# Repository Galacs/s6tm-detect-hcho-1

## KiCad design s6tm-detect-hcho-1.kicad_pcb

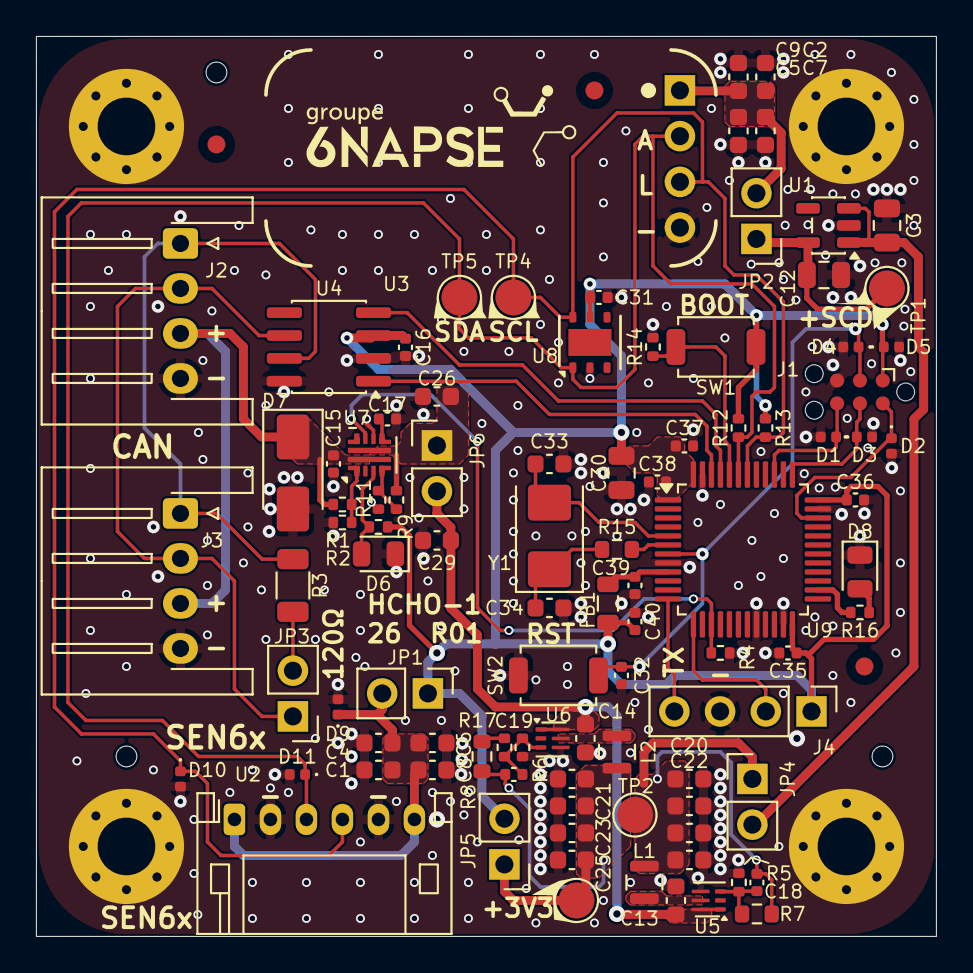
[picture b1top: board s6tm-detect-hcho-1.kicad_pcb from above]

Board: 2 copper layers, 50.0 x 50.0 mm, 106 parts (0 on the bottom side), 36 nets.

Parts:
C1, C2, C4, C5, C6, C7, C8, C9, C13, C14, C20, C21, C22, C23, C24, C25, C26, C27, C28, C29: 10u; C_0603_1608Metric
C3, C12, C30: 10u; C_0805_2012Metric
C15, C39, C40: 1u; C_0402_1005Metric
C16, C31, C32, C35, C36, C37, C38: 0u1; C_0402_1005Metric
C17: 1n; C_0402_1005Metric
C18, C19: 100p; C_0402_1005Metric
C33, C34: 20p; C_0603_1608Metric
D1, D2, D3, D4, D5, D9, D10, D11: H5VU10U; Diode_DFN1006
D6: GREEN; LED_0805_2012Metric
D7: SMAJ6.0CA; D_SMA
D8: YELLOW; LED_0805_2012Metric
FB1: 600Ω@100M; L_0805_2012Metric
FID1, FID2, FID3: Fiducial; Fiducial_1mm_Mask2mm
H1, H2, H3: MountingHole; ToolingHole_1.152mm
H4, H5, H6, H7: MountingHole_Pad; MountingHole_3.2mm_M3_Pad_Via
J1: TC2030; Tag-Connect_TC2030-IDC-NL_2x03_P1.27mm_Vertical
J2, J3: Conn_01x04; JST_XH_S4B-XH-A-1_1x04_P2.50mm_Horizontal
J4: Conn_01x04_Pin; PinHeader_1x04_P2.54mm_Vertical
JP1, JP2, JP3, JP4, JP5, JP6: Jumper_2_Small_Bridged; PinHeader_1x02_P2.54mm_Vertical
L1, L2: 0u47; TDK_TFM201610ALC
R1, R10, R12, R13, R14: 10k; R_0402_1005Metric
R2, R11: 4k7; R_0402_1005Metric
R3: 120; R_1206_3216Metric
R4: 3k3; R_0402_1005Metric
R5, R6: 100k; R_0402_1005Metric
R7: 510k; R_0603_1608Metric
R8: 430k; R_0603_1608Metric
R9, R16: 5k1; R_0402_1005Metric
R15: 560; R_0603_1608Metric
R17: 20k; R_0402_1005Metric
SW1, SW2: SW_Push; SW_SPST_TS-1088-xR020
TP1, TP2, TP3, TP4, TP5: TestPoint; TestPoint_Pad_D2.0mm
U1: TPS7A2033P; SOT-23-5
U2: SEN6x; JST_PH_S6B-PH-K_1x06_P2.00mm_Horizontal
U3: SCD43; Module_s6tm-scd4x-mod-1
U4: SN65HVD230; SOIC-8_3.9x4.9mm_P1.27mm
U5, U6: TPS6282x; Texas_VSON-6_1.5x1.5mm_P0.5mm_DMQ0006A
U7: TPS259472A; Texas_RPW0010A_VQFN-HR-10_2x2mm_P0.5mm
U8: HTU21; Texas_PWSON-N6
U9: STM32F103C8Tx; LQFP-48_7x7mm_P0.5mm
Y1: 8M; Crystal_SMD_5032-2Pin_5.0x3.2mm

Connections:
+3V3: C1.1, C4.1, C6.1, C8.1, C16.1, C19.1, C21.1, C23.1, C25.1, C28.1, C30.1, C31.2, C35.1, C36.1, C37.1, C38.1, C40.1, D5.1 (K), D9.1 (K), FB1.2, J1.1 (VCC), J4.1, JP1.1 (A), JP1.2 (B), JP5.1 (A), JP5.2 (B), L2.2, R8.1, R9.1, R12.1, R13.1, SW1.1, TP3.1 (1_1), U2.1 (VDD), U2.6 (VDD), U4.3 (VCC), U8.5 (VCC), U9.1 (VBAT), U9.24 (VDD), U9.36 (VDD), U9.48 (VDD)
+3V3_SCD: C2.1, C5.1, C7.1, C9.1, C12.1, JP2.1 (A), JP2.2 (B), TP1.1 (1_1), U1.5 (OUT), U3.7 (VDD)
+3V7: C3.1, C18.1, C20.1, C22.1, C24.1, C27.1, JP4.1 (A), JP4.2 (B), L1.2, R7.1, TP2.1 (1_1), U1.1 (IN), U1.3 (EN)
+5V: C13.1, C14.1, C26.1, C29.1, JP6.1 (A), JP6.2 (B), R10.2, U5.1 (EN), U5.6 (VIN), U6.1 (EN), U6.6 (VIN), U7.6 (OUT)
+5V_IN: C15.2, D7.1 (A1), J2.3, J3.3, R1.2, U7.5 (IN)
/BOOT: R14.2, SW1.2, U9.44 (BOOT0)
/CANH: J2.1, J3.1, R3.1, U4.7 (CANH)
/CANL: J2.2, J3.2, JP3.1 (A), U4.6 (CANL)
/CAN_RX: U4.4 (R), U9.45 (CAN_RX)
/CAN_TX: U4.1 (D), U9.46 (CAN_TX)
/ILM: R4.1, U7.9 (ILM), U9.15 (ADC1_IN5)
/NRST: C32.1, D4.1 (K), J1.3 (~RESET), SW2.2, U9.7 (NRST)
/SCL: D10.1 (K), R13.2, TP4.1 (1_1), U2.4 (SCL), U3.9 (SCL), U8.6 (SCL), U9.42 (I2C1_SCL)
/SDA: D11.1 (K), R12.2, TP5.1 (1_1), U2.3 (SDA), U3.10 (SDA), U8.1 (SDA), U9.43 (I2C1_SDA)
/SWCLK: D3.1 (K), J1.4 (SWCLK), U9.37 (SWCLK)
/SWDIO: D2.1 (K), J1.2 (SWDIO), U9.34 (SWDIO)
/SWO: D1.1 (K), J1.6 (SWO), U9.39 (TRACESWO)
/U0RXD: J4.2, U9.13 (USART2_RX)
/U0TXD: J4.4, U9.12 (USART2_TX)
/XTAL_I: C33.1, U9.5 (RCC_OSC_IN), Y1.2
/XTAL_O: R15.2, U9.6 (RCC_OSC_OUT)
/XTAL_RO: C34.1, R15.1, Y1.1
GND: C1.2, C2.2, C3.2, C4.2, C5.2, C6.2, C7.2, C8.2, C9.2, C12.2, C13.2, C14.2, C15.1, C16.2, C17.2, C20.2, C21.2, C22.2, C23.2, C24.2, C25.2, C26.2, C27.2, C28.2, C29.2, C30.2, C31.1, C32.2, C33.2, C34.2, C35.2, C36.2, C37.2, C38.2, C39.2, C40.2, D1.2 (A), D2.2 (A), D3.2 (A), D4.2 (A), D5.2 (A), D6.1 (K), D7.2 (A2), D8.1 (K), D9.2 (A), D10.2 (A), D11.2 (A), H4.1 (1_1), H5.1 (1_1), H6.1 (1_1), H7.1 (1_1), J1.5 (GND), J2.4, J3.4, J4.3, R2.1, R4.2, R5.2, R6.2, R11.1, R14.1, SW2.1, U1.2 (GND), U2.2 (GND), U2.5 (GND), U3.6 (GND), U4.2 (GND), U4.8 (Rs), U5.4 (GND), U6.4 (GND), U7.8 (GND), U8.2 (GND), U9.8 (VSSA), U9.20 (PB2), U9.23 (VSS), U9.35 (VSS), U9.47 (VSS)
unnamed: D6.2 (A), R9.2, U7.3 (PG)
unnamed: D8.2 (A), R16.2
unnamed: JP3.2 (B), R3.2
unnamed: R8.2, R17.2
unnamed: C18.2, R5.1, R7.2, U5.3 (FB)
unnamed: L1.1, U5.5 (SW)
unnamed: C19.2, R6.1, R17.1, U6.3 (FB)
unnamed: L2.1, U6.5 (SW)
unnamed: C17.1, U7.7 (DVDT)
unnamed: R1.1, R2.2, U7.1 (EN/UVLO)
unnamed: R10.1, R11.2, U7.4 (PGTH)
unnamed: R16.1, U9.26 (PB13)
unnamed: C39.1, FB1.1, U9.9 (VDDA)

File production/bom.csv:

Designator,Footprint,Quantity,Value,LCSC Part #
"C1, C13, C14, C2, C20, C21, C22, C23, C24, C25, C26, C27, C28, C29, C4, C5, C6, C7, C8, C9",0603,20,10u,C19702
"C12, C3, C30",0805,3,10u,C440198
"C15, C39, C40",0402,3,1u,C52923
"C16, C31, C32, C35, C36, C37, C38",0402,7,0u1,C307331
C17,0402,1,1n,C1523
"C18, C19",0402,2,100p,C1546
"C33, C34",0603,2,20p,C1648
"D1, D10, D11, D2, D3, D4, D5, D9",Diode_DFN1006,8,H5VU10U,C22395519
D6,0805,1,GREEN,C2297
D7,D_SMA,1,SMAJ6.0CA,C19077526
D8,0805,1,YELLOW,C2296
FB1,0805,1,600Ω@100M,C81034
"J2, J3",JST_XH_S4B-XH-A-1_1x04_P2.50mm_Horizontal,2,Conn_01x04,C163037
"L1, L2",TDK_TFM201610ALC,2,0u47,C89446
"R1, R10, R12, R13, R14",0402,5,10k,C25744
"R11, R2",0402,2,4k7,C25900
R15,0603,1,560,C23204
"R16, R9",0402,2,5k1,C25905
R17,0402,1,20k,C25765
R3,1206,1,120,C17909
R4,0402,1,3k3,C25890
"R5, R6",0402,2,100k,C25741
R7,0603,1,510k,C23192
R8,0603,1,430k,C25969
"SW1, SW2",SW_SPST_TS-1088-xR020,2,SW_Push,C720477
U1,SOT-23-5,1,TPS7A2033P,C2862740
U2,JST_PH_S6B-PH-K_1x06_P2.00mm_Horizontal,1,SEN6x,C157920
U4,SOIC-8_3.9x4.9mm_P1.27mm,1,SN65HVD230,C12084
"U5, U6",Texas_VSON-6_1.5x1.5mm_P0.5mm_DMQ0006A,2,TPS6282x,C2650334
U7,Texas_RPW0010A_VQFN-HR-10_2x2mm_P0.5mm,1,TPS259472A,C3662789
U8,Texas_PWSON-N6,1,HTU21,C83479
U9,LQFP-48_7x7mm_P0.5mm,1,STM32F103C8Tx,C8734
Y1,Crystal_SMD_5032-2Pin_5.0x3.2mm,1,8M,C115962
